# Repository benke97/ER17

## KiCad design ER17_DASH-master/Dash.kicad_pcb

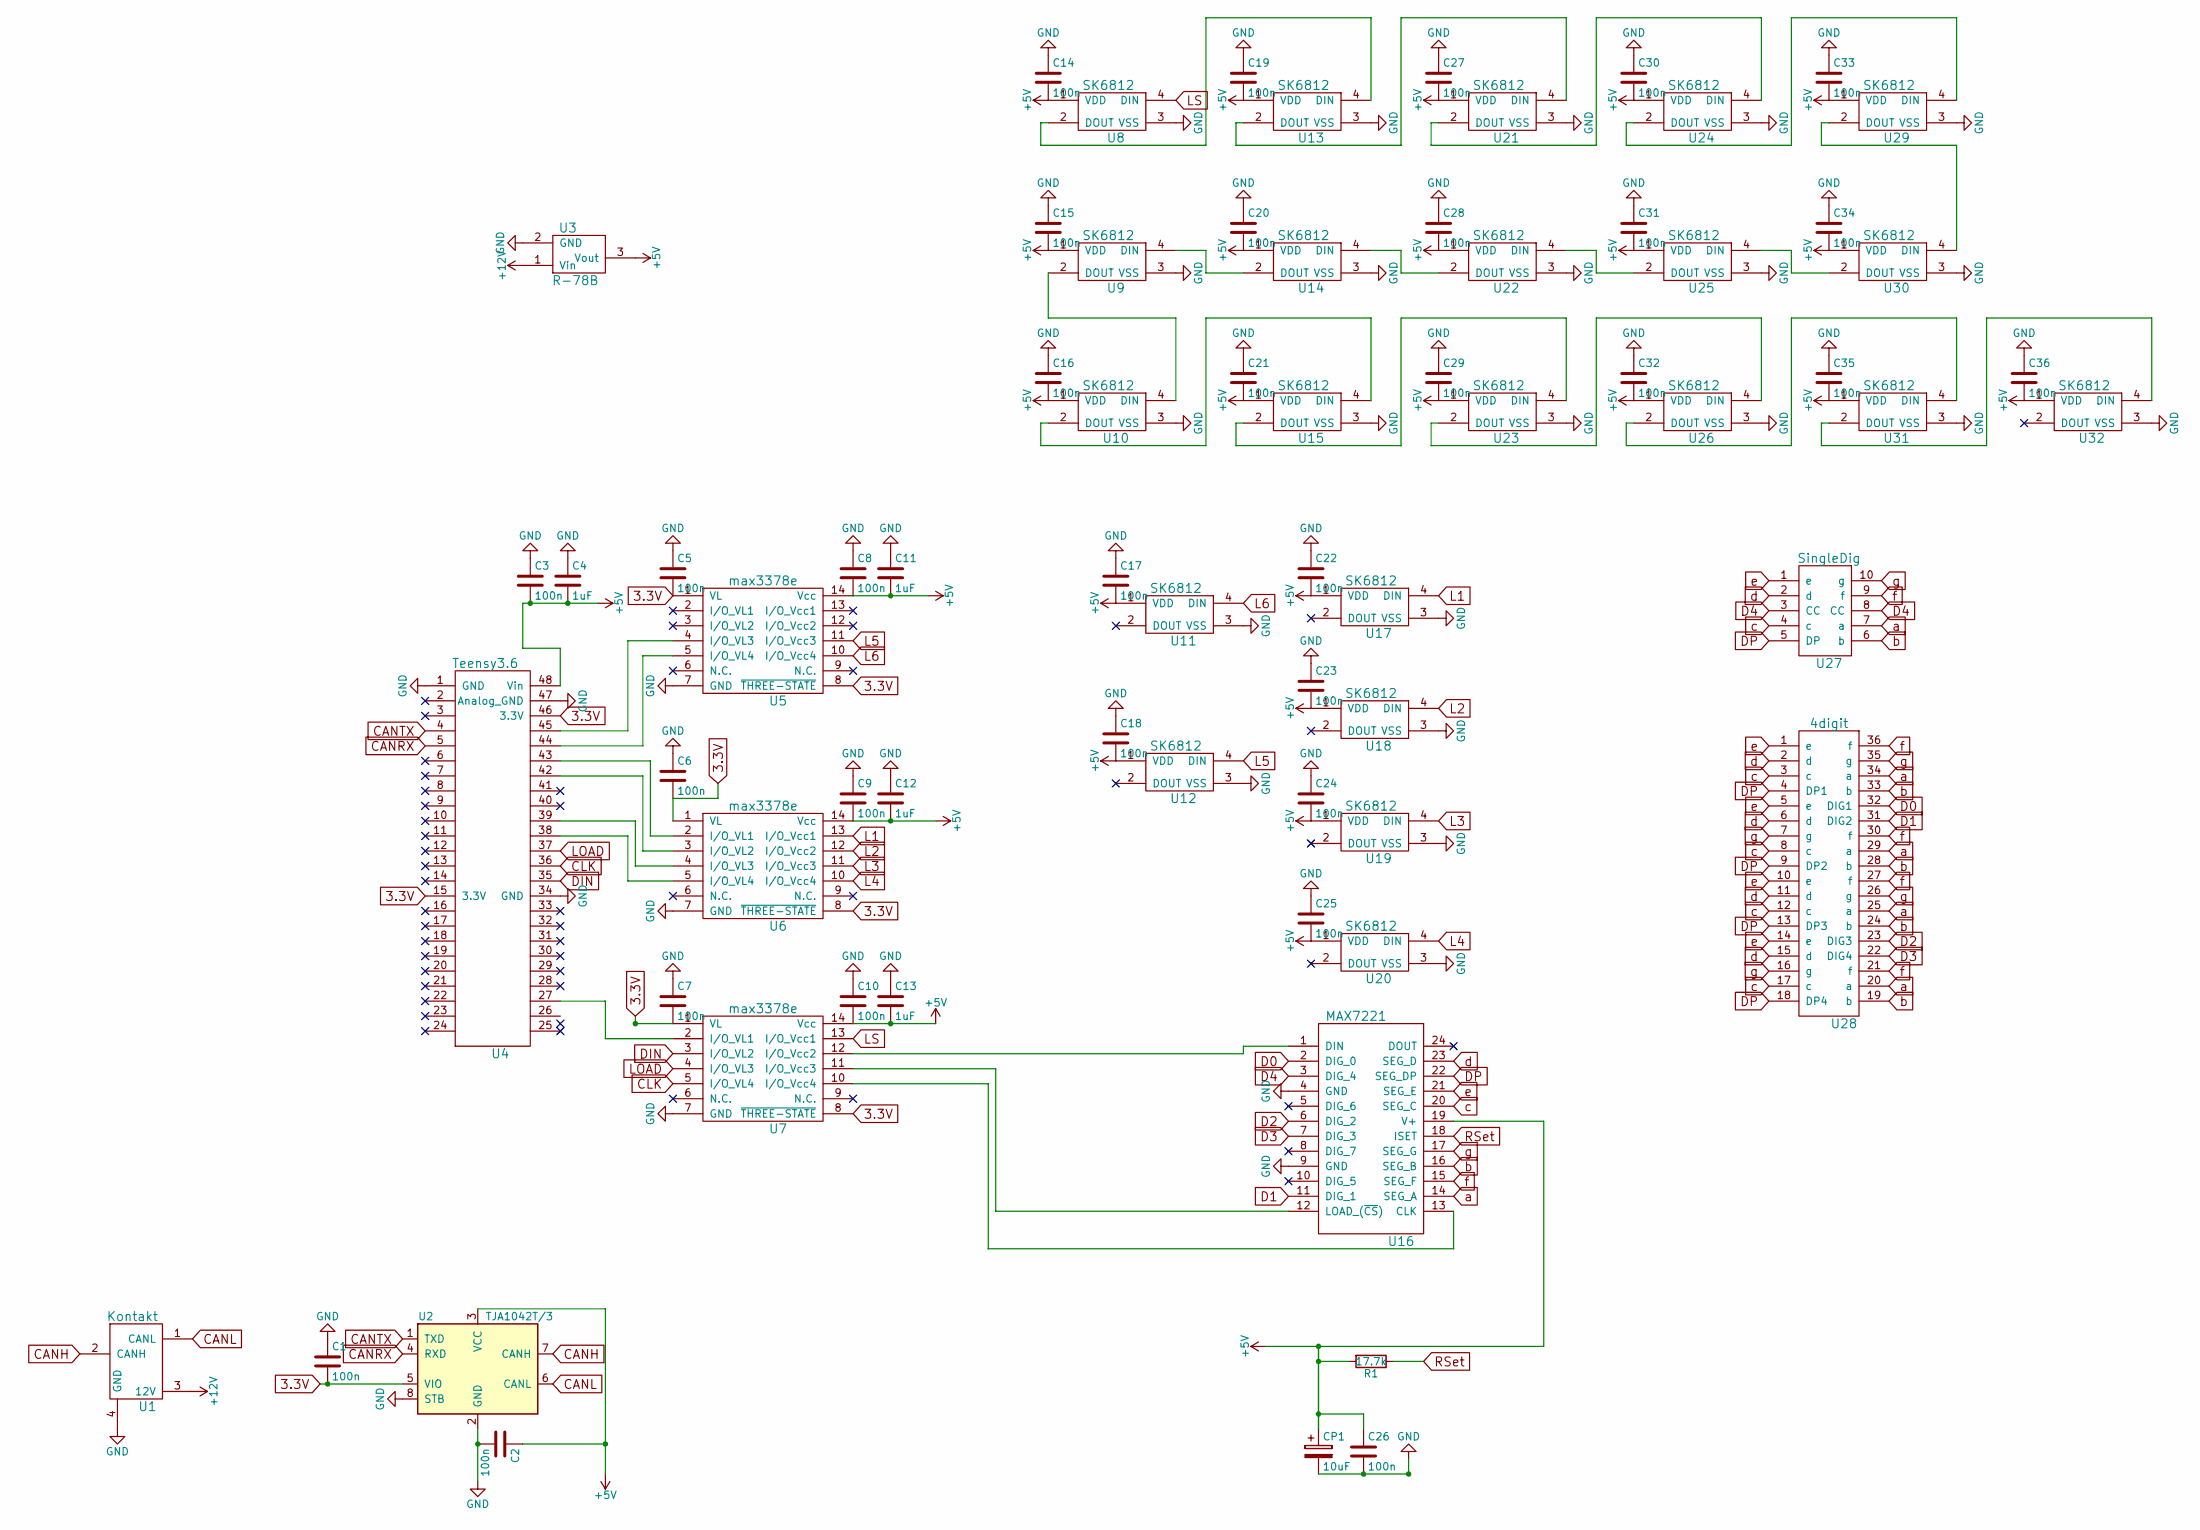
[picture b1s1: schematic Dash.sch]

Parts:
C1, C2, C3, C5, C6, C7, C8, C9, C10, C14, C15, C16, C17, C18, C19, C20, C21, C22, C23, C24, C25, C26, C27, C28, C29, C30, C31, C32, C33, C34, C35, C36: 100n; C_0805
C4, C11, C12, C13: 1uF; C_0805
CP1: 10uF; CP
R1: 17.7k; R_0805
U1: Kontakt
U2: TJA1042T/3; TJA1042T3
U3: R-78B
U4: Teensy3.6
U5, U6, U7: max3378e; MAX3378E
U8, U9, U10, U11, U12, U13, U14, U15, U17, U18, U19, U20, U21, U22, U23, U24, U25, U26, U29, U30, U31, U32: SK6812
U16: MAX7221
U27: SingleDig; SC10-21CGKWA
U28: 4digit; CC56-11EWA

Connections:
3.3V: C1.2, C5.2, C6.2, C7.2, U2.5 (VIO), U4.15 (3.3V), U4.46 (3.3V), U5.1 (VL), U5.8 (~THREE-STATE), U6.1 (VL), U6.8 (~THREE-STATE), U7.1 (VL), U7.8 (~THREE-STATE)
+5V: C2.1, C3.2, C4.2, C8.2, C9.2, C10.2, C11.2, C12.2, C13.2, C14.2, C15.2, C16.2, C17.2, C18.2, C19.2, C20.2, C21.2, C22.2, C23.2, C24.2, C25.2, C26.1, C27.2, C28.2, C29.2, C30.2, C31.2, C32.2, C33.2, C34.2, C35.2, C36.2, CP1.1, R1.2, U2.3 (VCC), U3.3 (Vout), U4.48 (Vin), U5.14 (Vcc), U6.14 (Vcc), U7.14 (Vcc), U8.1 (VDD), U9.1 (VDD), U10.1 (VDD), U11.1 (VDD), U12.1 (VDD), U13.1 (VDD), U14.1 (VDD), U15.1 (VDD), U16.19 (V+), U17.1 (VDD), U18.1 (VDD), U19.1 (VDD), U20.1 (VDD), U21.1 (VDD), U22.1 (VDD), U23.1 (VDD), U24.1 (VDD), U25.1 (VDD), U26.1 (VDD), U29.1 (VDD), U30.1 (VDD), U31.1 (VDD), U32.1 (VDD)
+12V: U1.3 (12V), U3.1 (Vin)
CANH: U1.2 (CANH), U2.7 (CANH)
CANL: U1.1 (CANL), U2.6 (CANL)
CANRX: U2.4 (RXD), U4.5
CANTX: U2.1 (TXD), U4.4
CLK: U4.36, U7.5 (I/O_VL4)
D0: U16.2 (DIG_0), U28.32 (DIG1)
D1: U16.11 (DIG_1), U28.31 (DIG2)
D2: U16.6 (DIG_2), U28.23 (DIG3)
D3: U16.7 (DIG_3), U28.22 (DIG4)
D4: U16.3 (DIG_4), U27.3 (CC), U27.8 (CC)
DIN: U4.35, U7.3 (I/O_VL2)
DP: U16.22 (SEG_DP), U27.5 (DP), U28.4 (DP1), U28.9 (DP2), U28.13 (DP3), U28.18 (DP4)
GND: C1.1, C2.2, C3.1, C4.1, C5.1, C6.1, C7.1, C8.1, C9.1, C10.1, C11.1, C12.1, C13.1, C14.1, C15.1, C16.1, C17.1, C18.1, C19.1, C20.1, C21.1, C22.1, C23.1, C24.1, C25.1, C26.2, C27.1, C28.1, C29.1, C30.1, C31.1, C32.1, C33.1, C34.1, C35.1, C36.1, CP1.2, U1.4 (GND), U2.2 (GND), U2.8 (STB), U3.2 (GND), U4.1 (GND), U4.34 (GND), U4.47 (Analog_GND), U5.7 (GND), U6.7 (GND), U7.7 (GND), U8.3 (VSS), U9.3 (VSS), U10.3 (VSS), U11.3 (VSS), U12.3 (VSS), U13.3 (VSS), U14.3 (VSS), U15.3 (VSS), U16.4 (GND), U16.9 (GND), U17.3 (VSS), U18.3 (VSS), U19.3 (VSS), U20.3 (VSS), U21.3 (VSS), U22.3 (VSS), U23.3 (VSS), U24.3 (VSS), U25.3 (VSS), U26.3 (VSS), U29.3 (VSS), U30.3 (VSS), U31.3 (VSS), U32.3 (VSS)
L1: U6.13 (I/O_Vcc1), U17.4 (DIN)
L2: U6.12 (I/O_Vcc2), U18.4 (DIN)
L3: U6.11 (I/O_Vcc3), U19.4 (DIN)
L4: U6.10 (I/O_Vcc4), U20.4 (DIN)
L5: U5.11 (I/O_Vcc3), U12.4 (DIN)
L6: U5.10 (I/O_Vcc4), U11.4 (DIN)
LOAD: U4.37, U7.4 (I/O_VL3)
LS: U7.13 (I/O_Vcc1), U8.4 (DIN)
unnamed: U4.27, U7.2 (I/O_VL1)
unnamed: U4.38, U6.5 (I/O_VL4)
unnamed: U4.39, U6.4 (I/O_VL3)
unnamed: U4.42, U6.3 (I/O_VL2)
unnamed: U4.43, U6.2 (I/O_VL1)
unnamed: U4.44, U5.5 (I/O_VL4)
unnamed: U4.45, U5.4 (I/O_VL3)
unnamed: U10.2 (DOUT), U15.4 (DIN)
unnamed: U9.2 (DOUT), U10.4 (DIN)
unnamed: U13.2 (DOUT), U21.4 (DIN)
unnamed: U8.2 (DOUT), U13.4 (DIN)
unnamed: U9.4 (DIN), U14.2 (DOUT)
unnamed: U14.4 (DIN), U22.2 (DOUT)
unnamed: U15.2 (DOUT), U23.4 (DIN)
unnamed: U7.12 (I/O_Vcc2), U16.1 (DIN)
unnamed: U7.11 (I/O_Vcc3), U16.12 (LOAD_(~CS))
unnamed: U7.10 (I/O_Vcc4), U16.13 (CLK)
unnamed: U21.2 (DOUT), U24.4 (DIN)
unnamed: U22.4 (DIN), U25.2 (DOUT)
unnamed: U23.2 (DOUT), U26.4 (DIN)
unnamed: U24.2 (DOUT), U29.4 (DIN)
unnamed: U25.4 (DIN), U30.2 (DOUT)
unnamed: U26.2 (DOUT), U31.4 (DIN)
unnamed: U29.2 (DOUT), U30.4 (DIN)
unnamed: U31.2 (DOUT), U32.4 (DIN)
RSet: R1.1, U16.18 (ISET)
a: U16.14 (SEG_A), U27.7 (a), U28.20 (a), U28.25 (a), U28.29 (a), U28.34 (a)
b: U16.16 (SEG_B), U27.6 (b), U28.19 (b), U28.24 (b), U28.28 (b), U28.33 (b)
c: U16.20 (SEG_C), U27.4 (c), U28.3 (c), U28.8 (c), U28.12 (c), U28.17 (c)
d: U16.23 (SEG_D), U27.2 (d), U28.2 (d), U28.6 (d), U28.11 (d), U28.15 (d)
e: U16.21 (SEG_E), U27.1 (e), U28.1 (e), U28.5 (e), U28.10 (e), U28.14 (e)
f: U16.15 (SEG_F), U27.9 (f), U28.21 (f), U28.27 (f), U28.30 (f), U28.36 (f)
g: U16.17 (SEG_G), U27.10 (g), U28.7 (g), U28.16 (g), U28.26 (g), U28.35 (g)

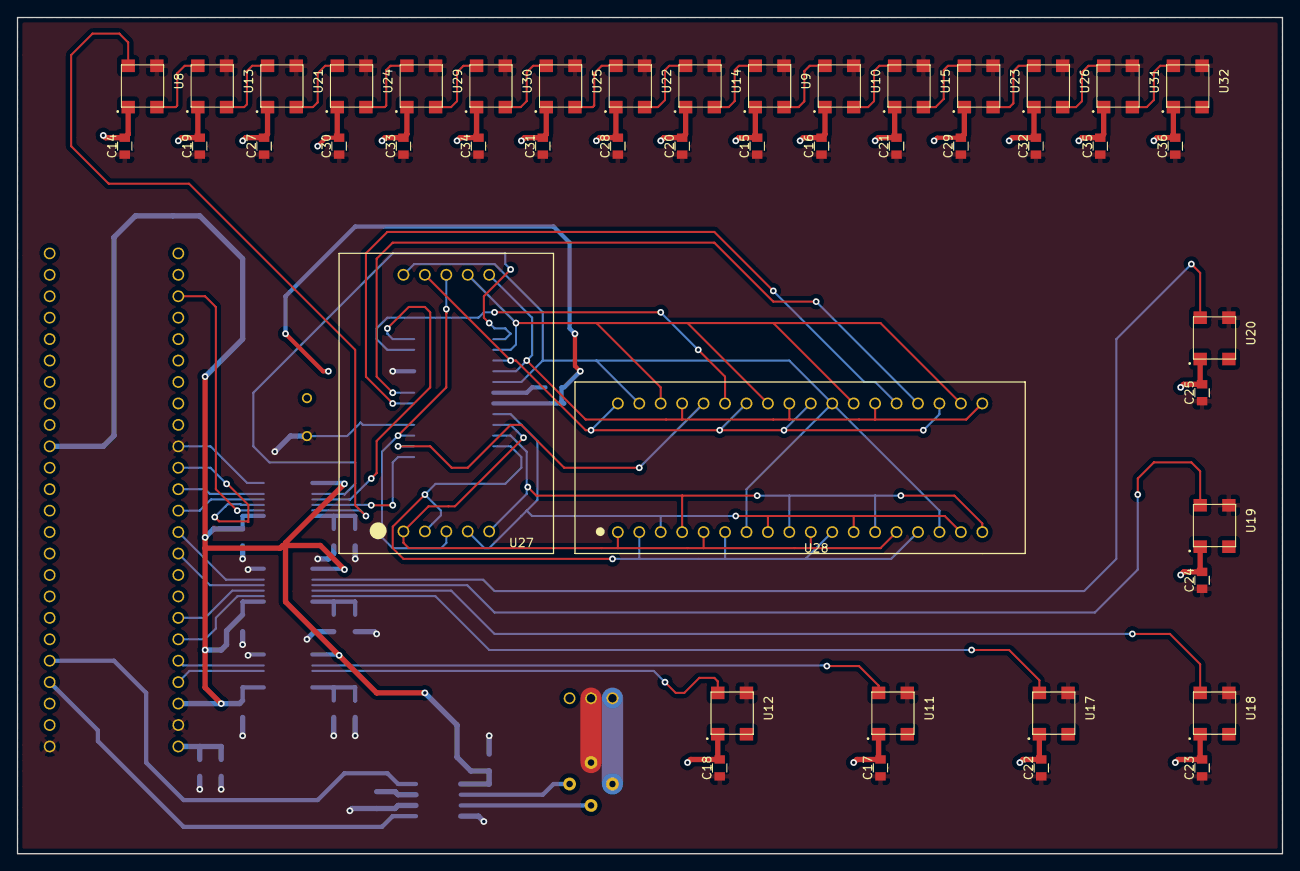
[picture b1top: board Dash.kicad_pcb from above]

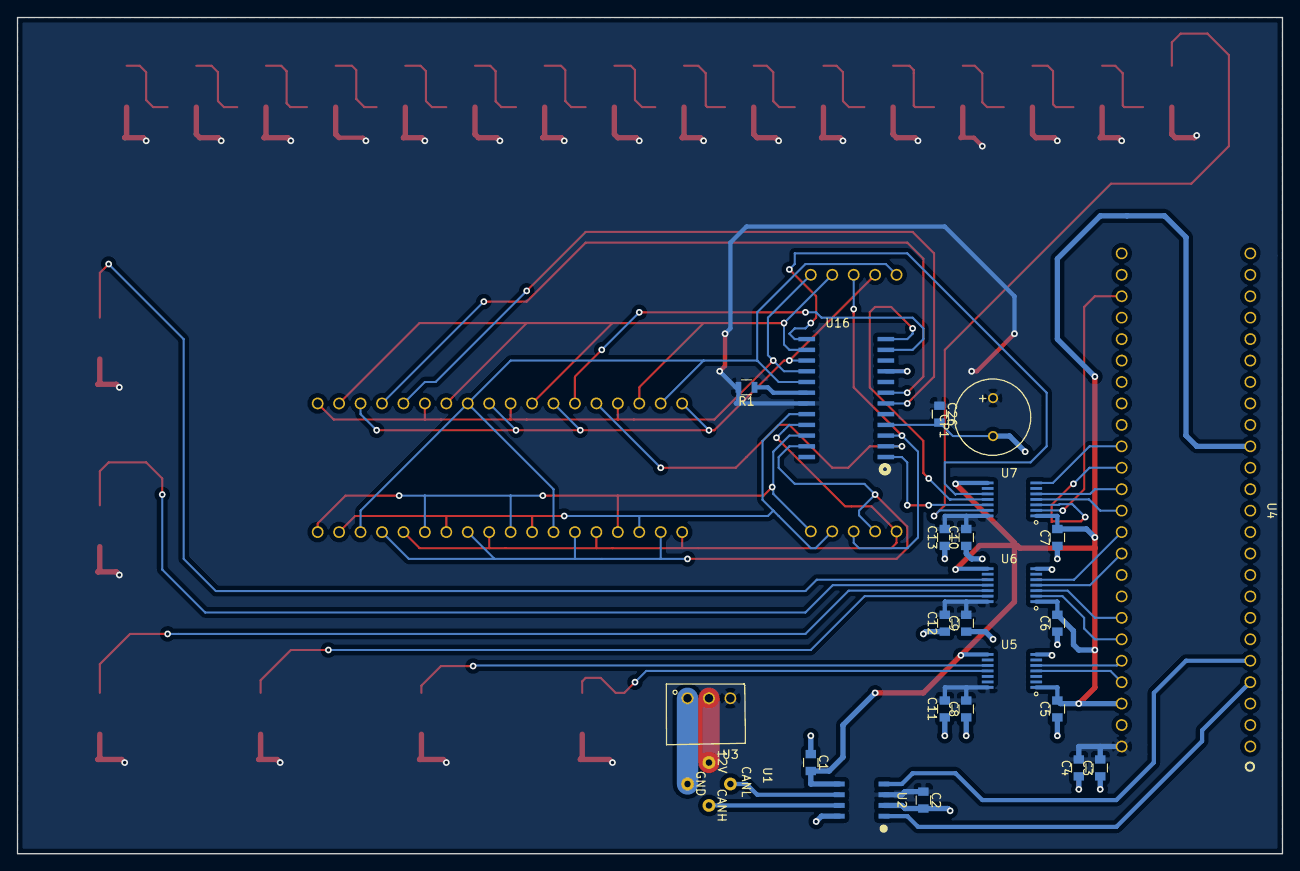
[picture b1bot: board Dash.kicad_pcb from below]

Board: 2 copper layers, 149.9 x 99.1 mm, 70 parts (24 on the bottom side), 57 nets.

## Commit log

2017-06-13 Dash 0 unconnected
2017-06-13 0 unconnected
2017-06-16 Typ klar
